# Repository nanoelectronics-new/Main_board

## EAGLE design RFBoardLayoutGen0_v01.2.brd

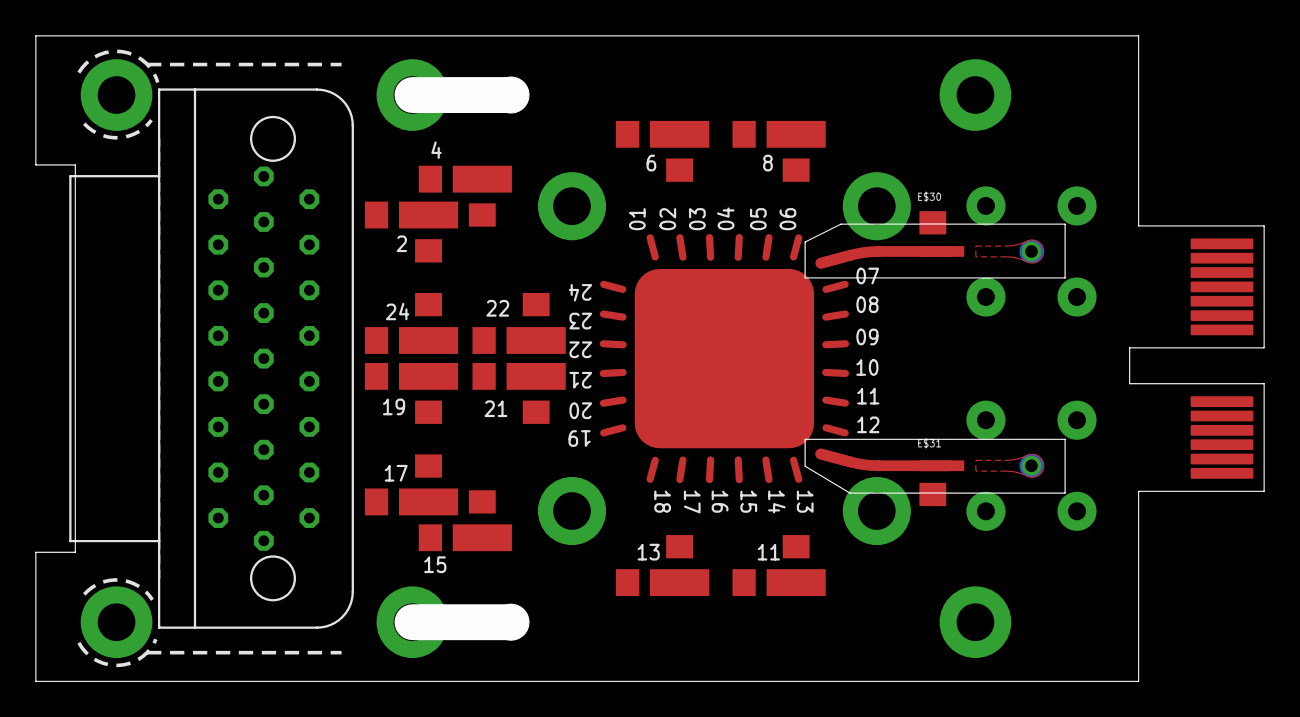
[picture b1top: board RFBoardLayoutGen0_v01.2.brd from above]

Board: 4 copper layers, 68.5 x 36.0 mm, 31 parts (0 on the bottom side), 50 nets.

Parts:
E$1: 24DC+4RF/400MU-PADS/10.0X10.0_V1.1
E$2: 25_SOCKET_M83513/13-D
E$3: MEC8-113-02-L-D-RA1
E$4, E$6, E$7, E$10, E$14, E$15: LP-FILTER/1_STAGE/OS/V1_01
E$5, E$8, E$9, E$11, E$12, E$13: LP-FILTER/1_STAGE/OS/V1_02
E$16, E$17, E$18, E$19, E$27, E$28: LP-FILTER/1_STAGE/OS/V1_03
E$20, E$21, E$22, E$23, E$24, E$25: LP-FILTER/1_STAGE/OS/V1_04
E$26, E$29: SMP_STRAIGHT_V02
E$30: BIAS_TEE_DOWN_V01
E$31: BIAS_TEE_UP_V01

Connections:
GND1: E$2.13, E$3.163, E$4.GND@1, E$5.GND@3, E$6.GND@1, E$7.GND@1, E$8.GND@3, E$9.GND@3, E$10.GND@1, E$11.GND@3, E$12.GND@3, E$13.GND@3, E$14.GND@1, E$15.GND@1, E$16.GND@3, E$17.GND@3, E$18.GND@3, E$19.GND@3, E$20.GND@1, E$21.GND@1, E$22.GND@1, E$23.GND@1, E$24.GND@1, E$25.GND@1, E$26.P$3, E$26.P$4, E$26.P$5, E$26.P$6, E$27.GND@3, E$28.GND@3, E$29.P$3, E$29.P$4, E$29.P$5, E$29.P$6
S$55: E$1.P$28, E$3.134, E$11.$4
S$67: E$2.24, E$11.$6
S$68: E$1.P$29, E$3.137, E$15.$2
S$76: E$2.11, E$15.$1
S$79: E$1.P$27, E$3.162, E$19.$4
S$80: E$2.12, E$19.$6
S$81: E$1.P$30, E$3.169, E$22.$2
S$83: E$2.23, E$22.$1
S$84: E$1.P$26, E$3.133, E$8.$4
S$85: E$2.25, E$8.$6
S$86: E$1.P$38, E$3.161, E$16.$4
S$88: E$2.01, E$16.$6
S$89: E$1.P$31, E$3.138, E$7.$2
S$90: E$2.10, E$7.$1
S$91: E$1.P$44, E$3.170, E$21.$2
S$95: E$2.22, E$21.$1
S$116: E$1.P$39, E$3.132, E$6.$2
S$144: E$2.14, E$6.$1
S$145: E$1.P$40, E$3.160, E$23.$2
S$146: E$2.02, E$23.$1
S$147: E$1.P$2, E$3.131, E$4.$2
S$149: E$2.15, E$4.$1
S$150: E$1.P$42, E$3.159, E$20.$2
S$151: E$2.03, E$20.$1
S$152: E$1.P$45, E$3.139, E$12.$4
S$154: E$2.09, E$12.$6
S$155: E$1.P$46, E$3.171, E$17.$4
S$156: E$2.21, E$17.$6
S$157: E$1.P$4, E$3.140, E$5.$4
S$158: E$2.08, E$5.$6
S$159: E$1.P$48, E$3.172, E$18.$4
S$160: E$2.20, E$18.$6
S$161: E$1.P$43, E$3.130, E$10.$2, E$30.P$1
S$162: E$2.16, E$10.$1
S$163: E$1.P$32, E$3.158, E$24.$2
S$164: E$2.04, E$24.$1
S$166: E$1.P$49, E$3.173, E$9.$4, E$31.P$1
S$167: E$1.P$33, E$3.129, E$14.$2
S$168: E$2.17, E$14.$1
S$169: E$1.P$34, E$3.157, E$25.$2
S$170: E$2.05, E$25.$1
S$171: E$2.07, E$9.$6
S$172: E$1.P$37, E$3.141, E$27.$4
S$173: E$2.19, E$27.$6
S$174: E$1.P$36, E$3.168, E$13.$4
S$175: E$2.06, E$13.$6
S$177: E$1.P$35, E$3.136, E$28.$4
S$178: E$2.18, E$28.$6
S$181: E$1.BASE, E$3.135

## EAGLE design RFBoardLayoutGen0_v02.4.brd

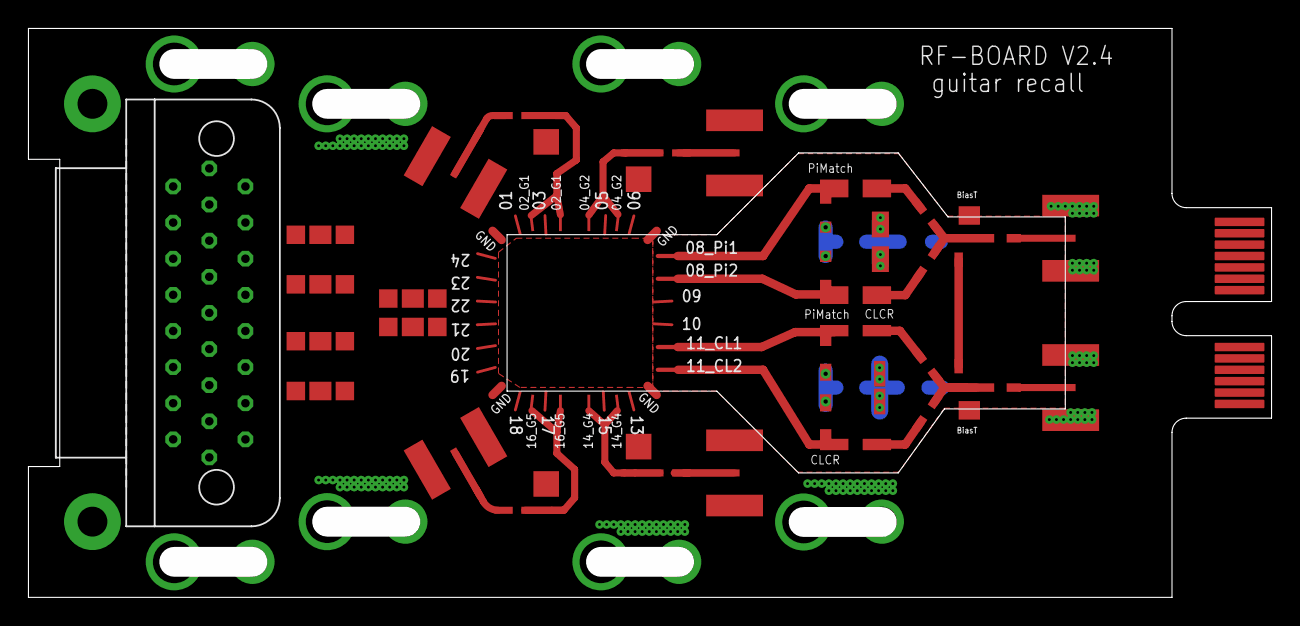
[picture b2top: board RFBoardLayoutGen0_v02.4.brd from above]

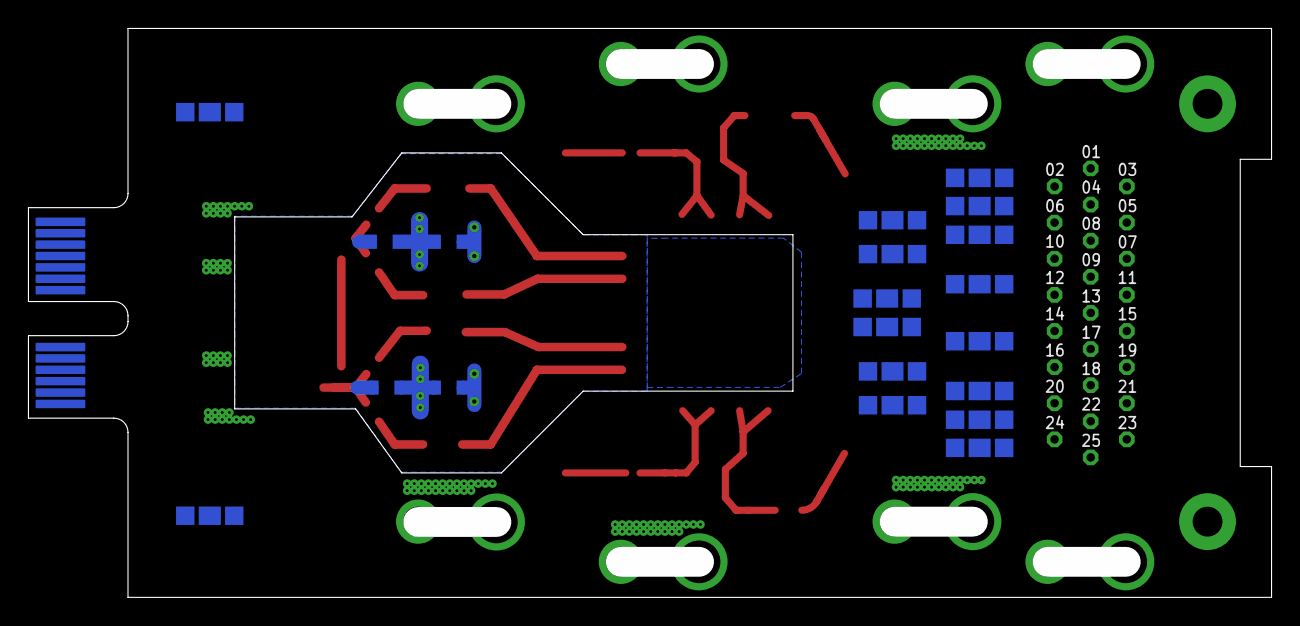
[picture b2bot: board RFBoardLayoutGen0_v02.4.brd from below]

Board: 4 copper layers, 87.4 x 40.0 mm, 61 parts (14 on the bottom side), 45 nets.

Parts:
B$1, B$4: BIAS_TEE_DOWN_0603
B$2, B$5: BIAS_TEE_UP_0603
E$1: 24DC+4RF/400MU-PADS/10.0X10.0_V1.5
E$2: 25_SOCKET_M83513/13-D
E$3: MEC8-113-02-L-D-RA1
E$4, E$5, E$6, E$7, E$8, E$11, E$12, E$13, E$14, E$15: LP-FILTER/1_STAGE/OS/0603_TOP_V1_01
E$9: PI_MATCH_V01_UP
E$10: CLCR_V01_DOWN
E$16, E$17, E$18, E$19, E$20, E$21, E$22, E$23, E$24, E$25, E$27, E$28: LP-FILTER/1_STAGE/OS/0603_BOTTOM_V1_01
E$26, E$33: SMP_STRAIGHT_MINI_WIDE_V1_01
E$29: BIAS_TEE_UP_V01
E$30: BIAS_TEE_DOWN_V01
E$31, E$34, E$35, E$36, E$38, E$39, E$40, E$41, E$42, E$43, E$44, E$45, E$46, E$47, E$48, E$49, E$50, E$51, E$52, E$54: SMD1-0,6
E$32: PI_MATCH_V01_DOWN
E$37: CLCR_V01_UP
S$2, S$3, S$6, S$7: MC-921SMALL; SMP_STRAIGHT_MINI_WIDE

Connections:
D$2: B$1.LF, E$3.19, E$6.$2
D$4: B$2.LF, E$3.21, E$4.$2
GND: E$1.P$1, E$1.P$3, E$1.P$6, E$2.13, E$3.14, E$4.GND@1, E$5.GND@1, E$6.GND@1, E$7.GND@1, E$8.GND@1, E$11.GND@1, E$12.GND@1, E$13.GND@1, E$14.GND@1, E$15.GND@1, E$16.GND@1, E$17.GND@1, E$18.GND@1, E$19.GND@1, E$20.GND@1, E$21.GND@1, E$22.GND@1, E$23.GND@1, E$24.GND@1, E$25.GND@1, E$26.GND, E$26.GND@1, E$27.GND@1, E$28.GND@1, E$33.GND, E$33.GND@1, S$2.2@1, S$2.2@2, S$3.2@1, S$3.2@2, S$6.2@1, S$6.2@2, S$7.2@1, S$7.2@2
S$1: E$1.P$30, E$22.$2
S$2: E$1.P$44, E$3.8, E$21.$2, E$47.1
S$55: E$1.P$49, E$3.2, E$27.$2, E$46.1
S$67: E$2.24, E$11.$1
S$68: E$1.P$29, E$3.9, E$15.$2
S$76: E$2.11, E$15.$1
S$79: E$1.P$27, E$3.16, E$19.$2
S$80: E$2.12, E$19.$1
S$83: E$2.23, E$22.$1
S$84: E$1.P$26, E$3.17, E$8.$2
S$85: E$2.25, E$8.$1
S$86: E$1.P$38, E$3.18, E$16.$2, E$36.1
S$88: E$2.01, E$16.$1
S$89: E$1.P$31, E$3.7, E$7.$2
S$90: E$2.10, E$7.$1
S$95: E$2.22, E$21.$1
S$144: E$2.14, E$6.$1
S$145: E$1.P$40, E$3.20, E$23.$2
S$146: E$2.02, E$23.$1
S$147: B$5.LF, E$3.6, E$17.$2
S$149: E$2.15, E$4.$1
S$150: E$1.P$42, E$3.24, E$20.$2
S$151: E$2.03, E$20.$1
S$152: E$1.P$45, E$3.5, E$12.$2
S$154: E$2.09, E$12.$1
S$155: B$4.LF, E$3.4, E$18.$2
S$156: E$2.21, E$17.$1
S$157: E$1.P$4, E$3.3, E$5.$2
S$158: E$2.08, E$5.$1
S$160: E$2.20, E$18.$1
S$162: E$2.16, E$24.$1
S$168: E$2.17, E$14.$1
S$169: E$1.P$34, E$3.26, E$25.$2
S$170: E$2.05, E$25.$1
S$171: E$2.07, E$27.$1
S$174: E$1.P$28, E$3.15, E$11.$2
S$175: E$2.06, E$13.$1
S$177: E$1.P$35, E$3.11, E$28.$2
S$178: E$2.18, E$28.$1
S$183: E$3.12, E$13.$2, E$29.P$1
S$190: E$3.23, E$14.$2, E$30.P$1
S$211: E$1.P$43, E$3.22, E$24.$2, E$34.1
